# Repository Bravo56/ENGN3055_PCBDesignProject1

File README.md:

# ENGN3055_PCBDesignProject1
JWU ENGN3055 Spring 2018

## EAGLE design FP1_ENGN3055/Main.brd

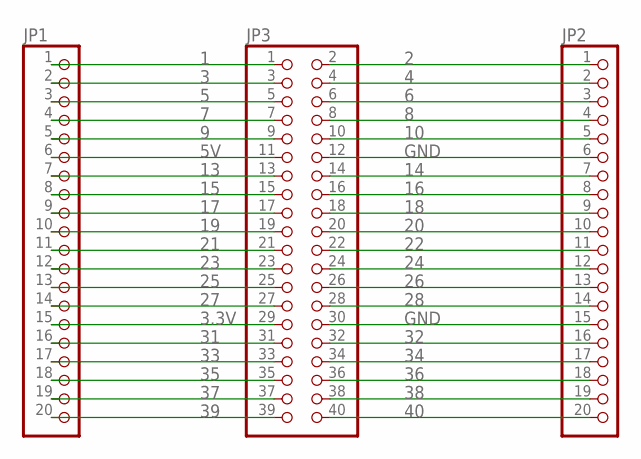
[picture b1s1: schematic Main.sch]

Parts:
JP1, JP2: PINHD-1X20; 1X20
JP3: PINHD-2X20; 2X20

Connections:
1: JP1.1, JP3.1
2: JP2.1, JP3.2
3: JP1.2, JP3.3
3.3V: JP1.15, JP3.29
4: JP2.2, JP3.4
5: JP1.3, JP3.5
5V: JP1.6, JP3.11
6: JP2.3, JP3.6
7: JP1.4, JP3.7
8: JP2.4, JP3.8
9: JP1.5, JP3.9
10: JP2.5, JP3.10
13: JP1.7, JP3.13
14: JP2.7, JP3.14
15: JP1.8, JP3.15
16: JP2.8, JP3.16
17: JP1.9, JP3.17
18: JP2.9, JP3.18
19: JP1.10, JP3.19
20: JP2.10, JP3.20
21: JP1.11, JP3.21
22: JP2.11, JP3.22
23: JP1.12, JP3.23
24: JP2.12, JP3.24
25: JP1.13, JP3.25
26: JP2.13, JP3.26
27: JP1.14, JP3.27
28: JP2.14, JP3.28
31: JP1.16, JP3.31
32: JP2.16, JP3.32
33: JP1.17, JP3.33
34: JP2.17, JP3.34
35: JP1.18, JP3.35
36: JP2.18, JP3.36
37: JP1.19, JP3.37
38: JP2.19, JP3.38
39: JP1.20, JP3.39
40: JP2.20, JP3.40
GND: JP2.6, JP2.15, JP3.12, JP3.30

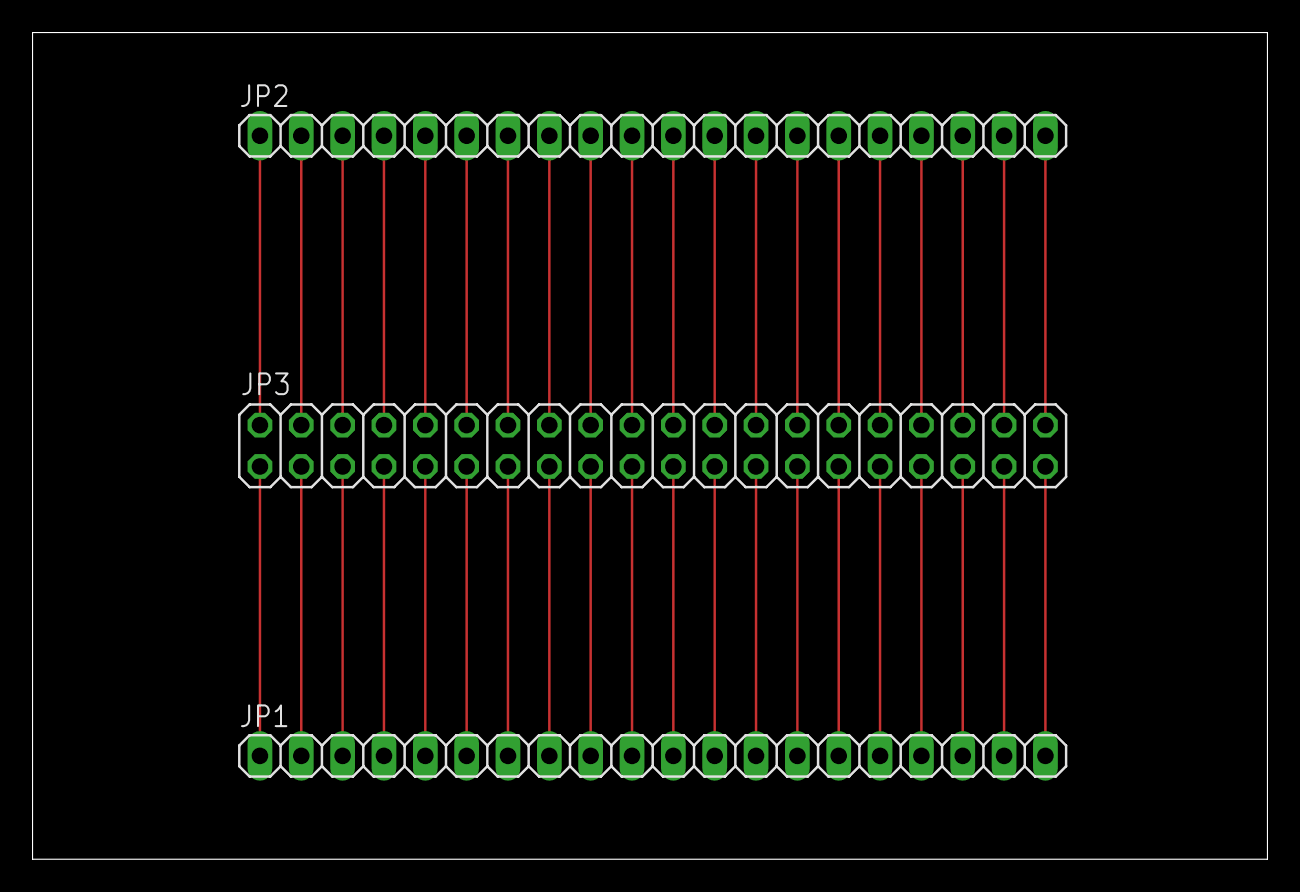
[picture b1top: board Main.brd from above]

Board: 2 copper layers, 75.9 x 50.8 mm, 3 parts (0 on the bottom side), 39 nets.
